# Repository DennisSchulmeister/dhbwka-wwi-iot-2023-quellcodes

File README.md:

Quellcodes zum Wahlmodul „IoT - Hardwarenahe Programmierung”
============================================================

Kurzbeschreibung
----------------

Dieses Repository beinhaltet sämtliche zur Verfügung gestellten Quellcodes,
Aufgaben und Praxisbeispiele des Wahlmoduls „IoT – Hardwarenahe Programmierung”
im Studiengang Wirtschaftsinformatik an der DHBW Karlsruhe.

Copyright
---------

Sämtliche Quellcodes sind lizenziert unter
[_Creative Commons Namensnennung 4.0 International_](http://creativecommons.org/licenses/by/4.0/)

© 2023 Dennis Schulmeister-Zimolong <br/>

E-Mail: [dhbw@windows3.de](mailto:dhbw@windows3.de) <br/>
Webseite: https://www.wpvs.de

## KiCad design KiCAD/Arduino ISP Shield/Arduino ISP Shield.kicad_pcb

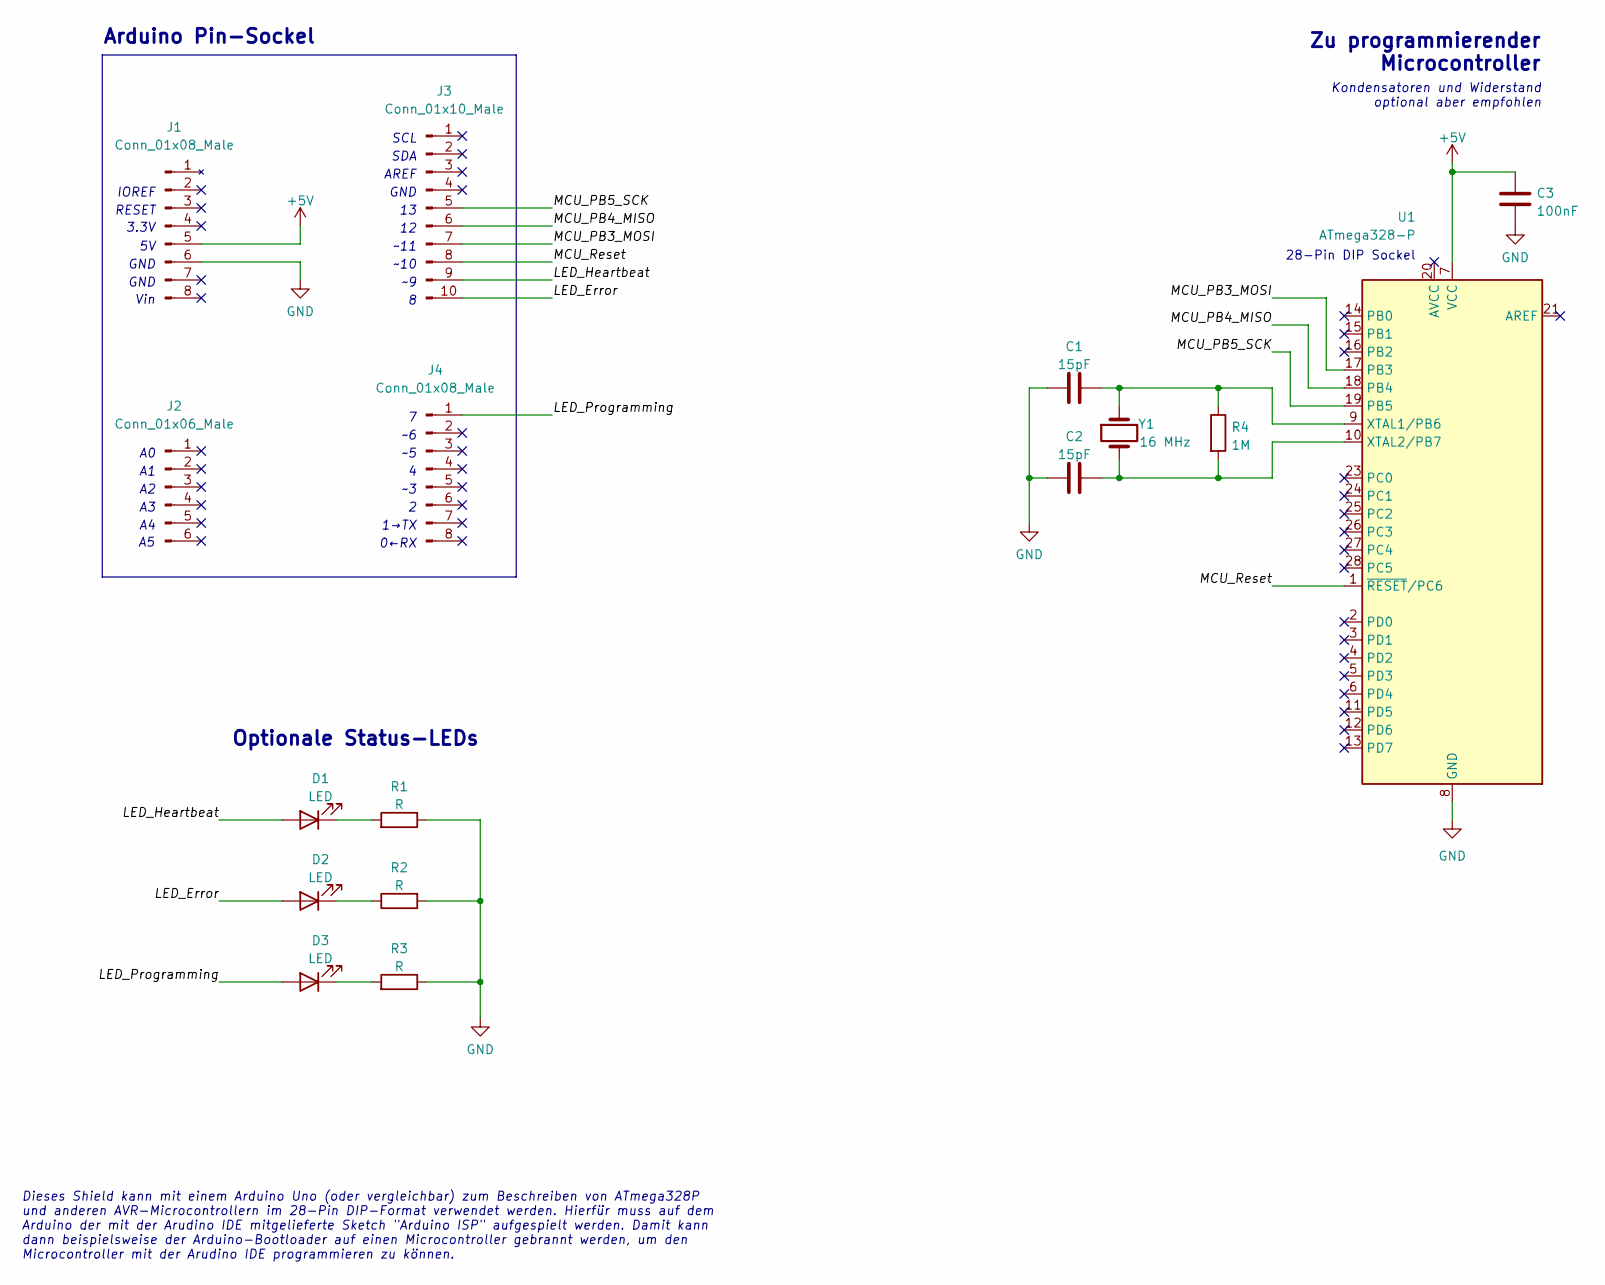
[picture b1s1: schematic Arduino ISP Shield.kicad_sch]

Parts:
C1, C2: 15pF; C_Disc_D5.0mm_W2.5mm_P5.00mm
C3: 100nF; C_Disc_D5.0mm_W2.5mm_P5.00mm
D1, D2, D3: LED; LED_D5.0mm
J1, J4: Conn_01x08_Male; PinHeader_1x08_P2.54mm_Vertical
J2: Conn_01x06_Male; PinHeader_1x06_P2.54mm_Vertical
J3: Conn_01x10_Male; PinHeader_1x10_P2.54mm_Vertical
R1, R2, R3: R; R_Axial_DIN0207_L6.3mm_D2.5mm_P7.62mm_Horizontal
R4: 1M; R_Axial_DIN0207_L6.3mm_D2.5mm_P7.62mm_Horizontal
U1: ATmega328-P; DIP-28_W7.62mm
Y1: 16 MHz; Resonator-2Pin_W8.0mm_H3.5mm

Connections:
+5V: C3.1, J1.5, U1.7 (VCC)
/LED_Error: D2.2 (A), J3.10
/LED_Heartbeat: D1.2 (A), J3.9
/LED_Programming: D3.2 (A), J4.1
/MCU_PB3_MOSI: J3.7, U1.17 (PB3)
/MCU_PB4_MISO: J3.6, U1.18 (PB4)
/MCU_PB5_SCK: J3.5, U1.19 (PB5)
/MCU_Reset: J3.8, U1.1 (~RESET/PC6)
GND: C1.1, C2.1, C3.2, J1.6, R1.1, R2.2, R3.1, U1.8 (GND), U1.22 (GND)
unnamed: C1.2, R4.1, U1.9 (XTAL1/PB6), Y1.1
unnamed: C2.2, R4.2, U1.10 (XTAL2/PB7), Y1.2
unnamed: D1.1 (K), R1.2
unnamed: D2.1 (K), R2.1
unnamed: D3.1 (K), R3.2

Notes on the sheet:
SCL
Kondensatoren und Widerstand optional aber empfohlen
Vin
Dieses Shield kann mit einem Arduino Uno (oder vergleichbar) zum Beschreiben von ATmega328P und anderen AVR-Microcontrollern im 28-Pin DIP-Format verwendet werden. Hierfür muss auf dem Arduino der mit der Arudino IDE mitgelieferte Sketch "Arduino ISP" aufgespielt werden. Damit kann dann beispielswe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
Arduino Pin-Sockel
SDA
0←RX
GND
AREF
Optionale Status-LEDs
Zu programmierender Microcontroller
28-Pin DIP Sockel
~10
IOREF
3.3V
~11
RESET
1→TX

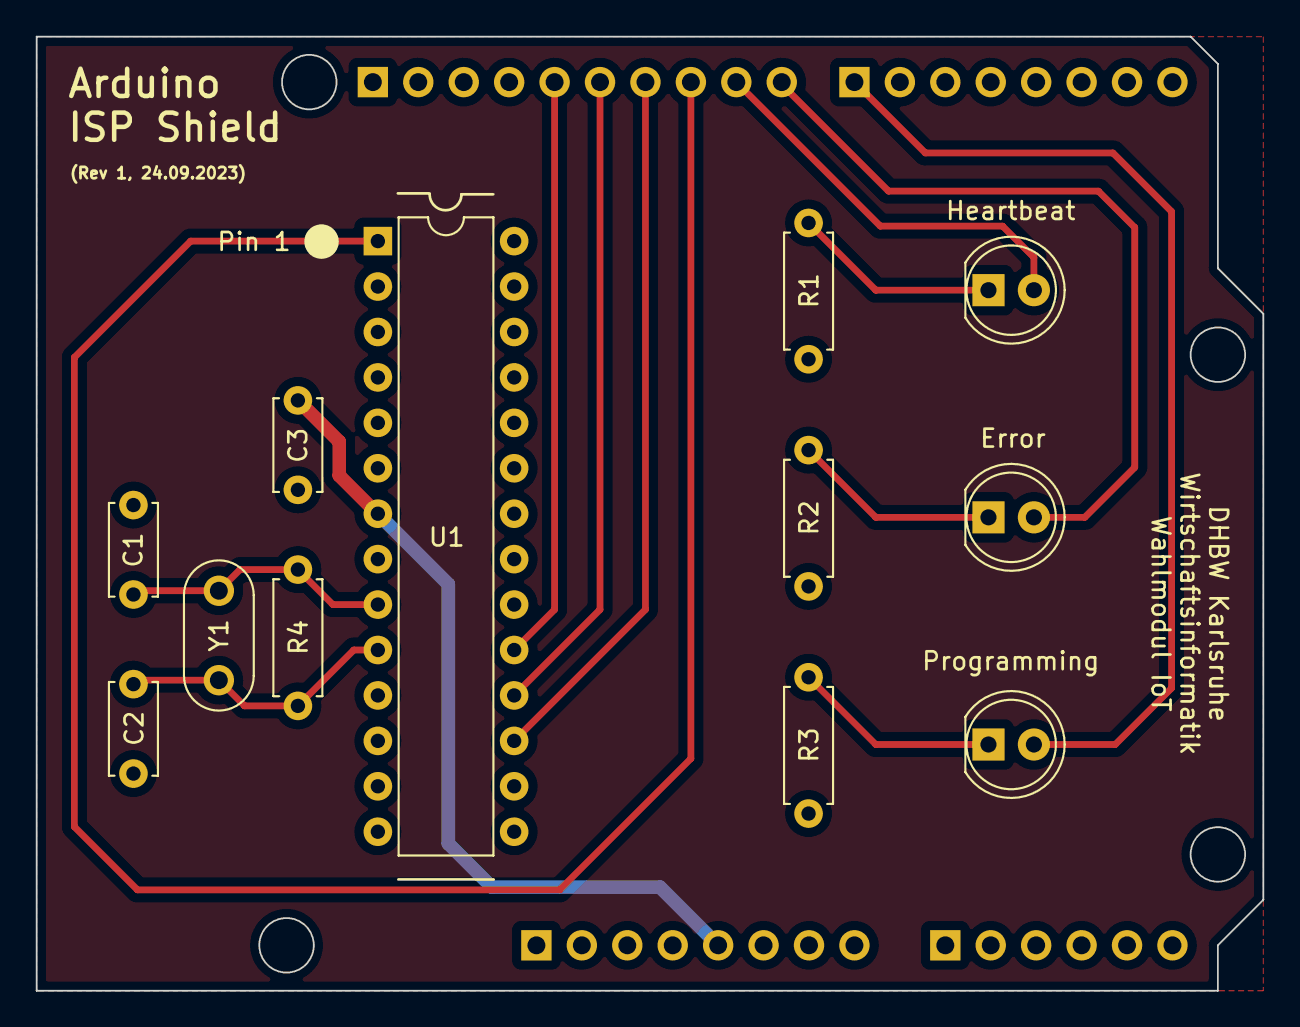
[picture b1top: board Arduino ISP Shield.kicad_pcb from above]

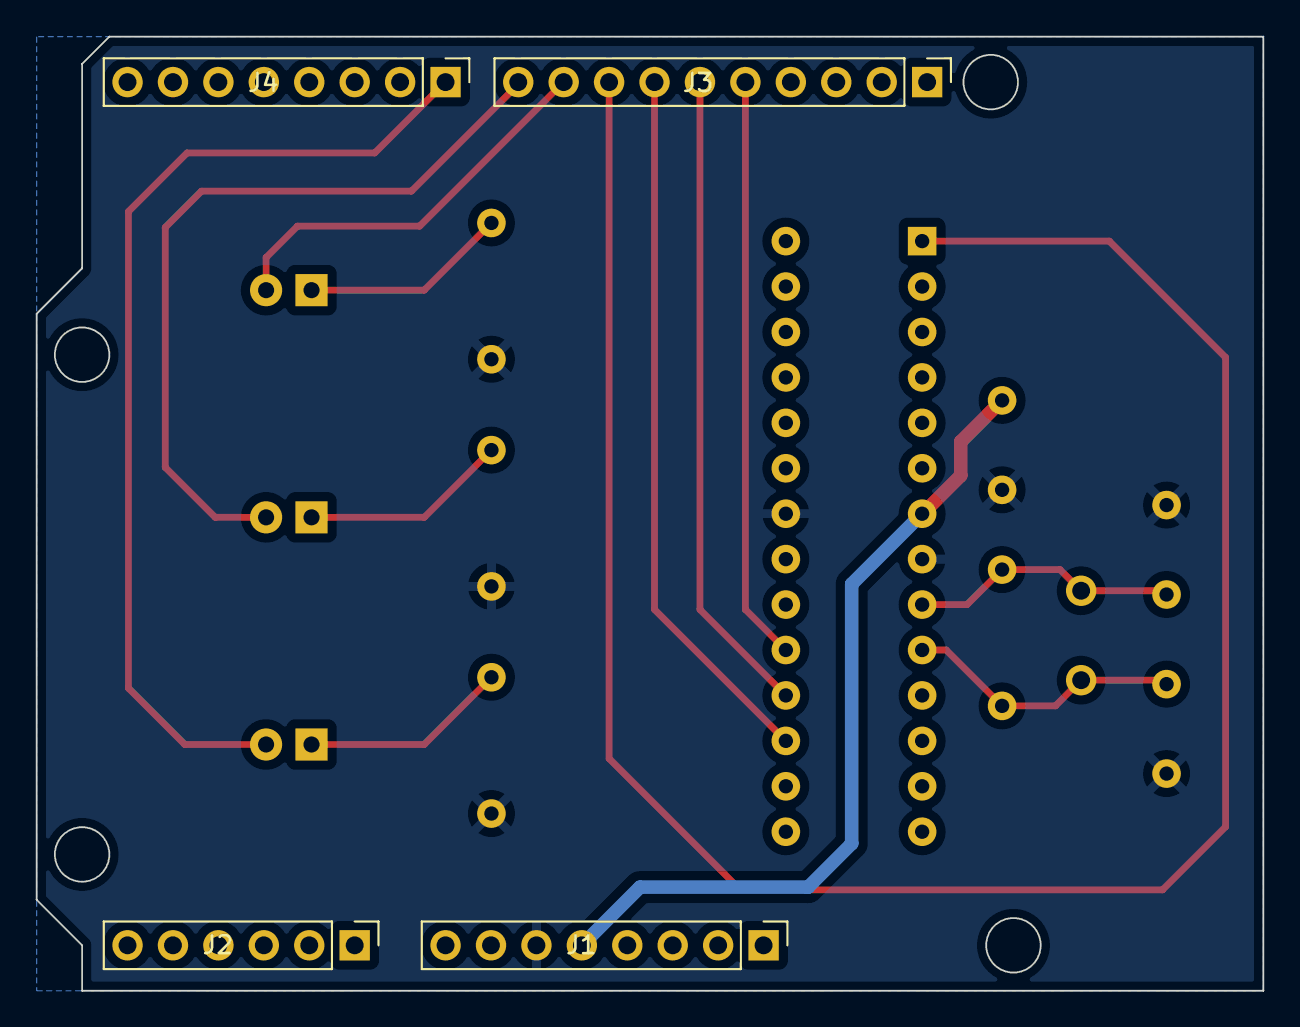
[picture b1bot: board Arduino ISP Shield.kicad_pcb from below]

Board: 2 copper layers, 68.6 x 53.3 mm, 16 parts (4 on the bottom side), 14 nets.

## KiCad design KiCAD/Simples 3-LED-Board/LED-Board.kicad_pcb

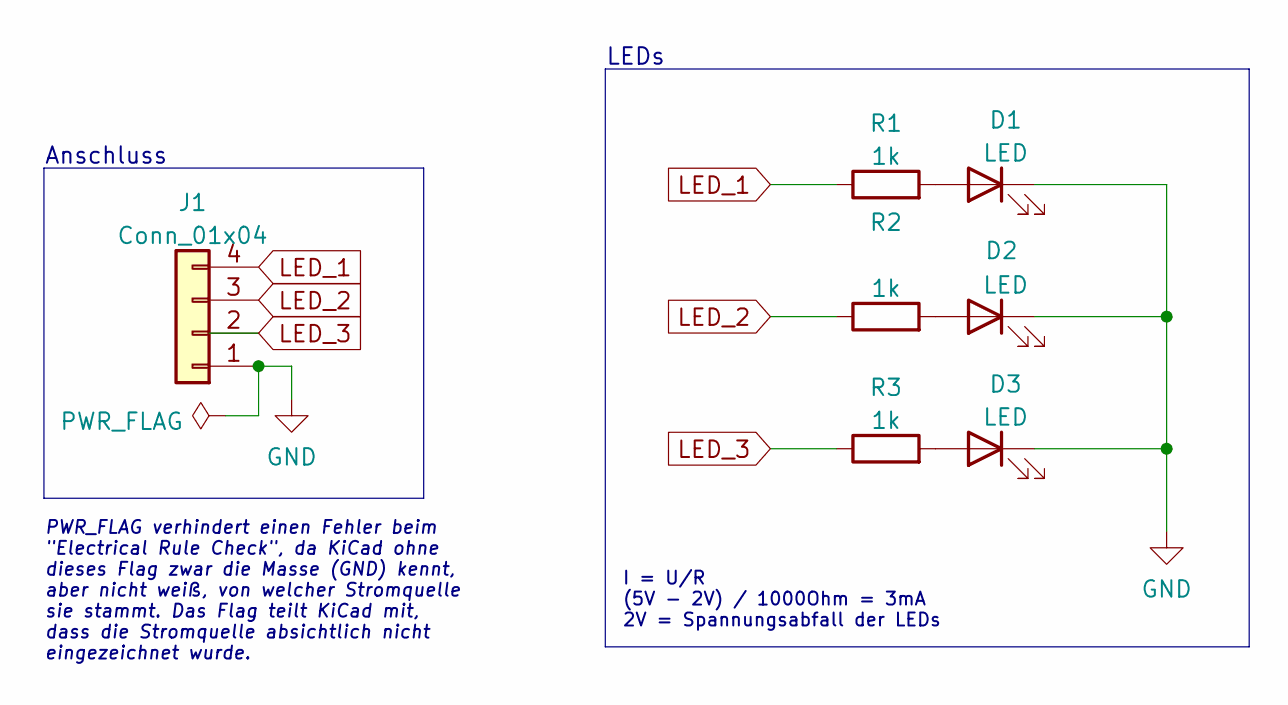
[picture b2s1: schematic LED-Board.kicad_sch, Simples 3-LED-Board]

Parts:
D1, D2, D3: LED; LED_D3.0mm
J1: Conn_01x04; PinHeader_1x04_P2.54mm_Vertical
R1, R2, R3: 1k; R_Axial_DIN0204_L3.6mm_D1.6mm_P5.08mm_Horizontal

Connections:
GND: D1.1 (K), D2.1 (K), D3.1 (K), J1.1
LED_1: J1.4, R1.1
LED_2: J1.3, R2.1
LED_3: J1.2, R3.1
unnamed: D1.2 (A), R1.2
unnamed: D2.2 (A), R2.2
unnamed: D3.2 (A), R3.2

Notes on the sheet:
I = U/R (5V - 2V) / 1000Ohm = 3mA 2V = Spannungsabfall der LEDs
Anschluss
PWR_FLAG verhindert einen Fehler beim "Electrical Rule Check", da KiCad ohne dieses Flag zwar die Masse (GND) kennt, aber nicht weiß, von welcher Stromquelle sie stammt. Das Flag teilt KiCad mit, dass die Stromquelle absichtlich nicht eingezeichnet wurde.
LEDs

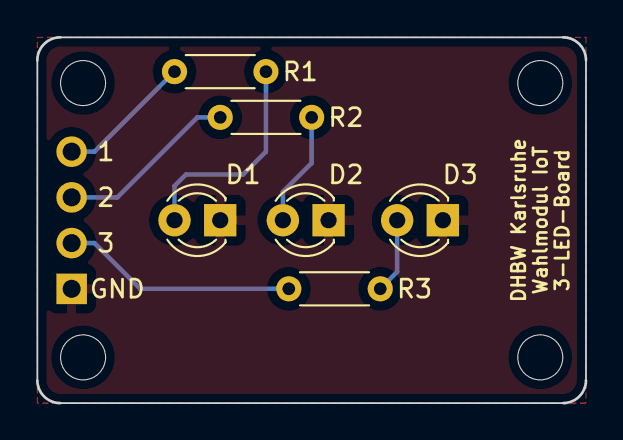
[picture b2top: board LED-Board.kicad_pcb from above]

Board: 2 copper layers, 30.5 x 20.3 mm, 11 parts (1 on the bottom side), 7 nets.

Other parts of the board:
H1, H2, H3, H4: MountingHole; MountingHole_2.5mm

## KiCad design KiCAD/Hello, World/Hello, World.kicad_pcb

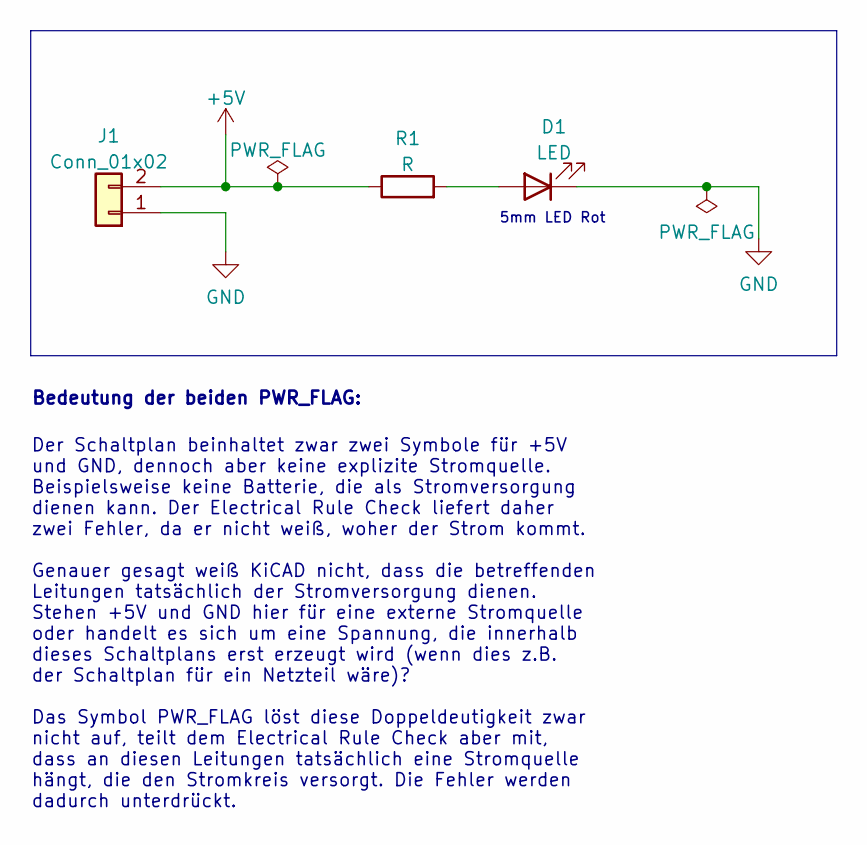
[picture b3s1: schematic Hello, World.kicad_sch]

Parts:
D1: LED; LED_D8.0mm
J1: Conn_01x02; TerminalBlock_bornier-2_P5.08mm
R1: R; R_Axial_DIN0204_L3.6mm_D1.6mm_P5.08mm_Horizontal

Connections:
+5V: J1.2, R1.1
GND: D1.1 (K), J1.1
unnamed: D1.2 (A), R1.2

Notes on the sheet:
Bedeutung der beiden PWR_FLAG:
Der Schaltplan beinhaltet zwar zwei Symbole für +5V und GND, dennoch aber keine explizite Stromquelle. Beispielsweise keine Batterie, die als Stromversorgung dienen kann. Der Electrical Rule Check liefert daher zwei Fehler, da er nicht weiß, woher der Strom kommt. Genauer gesagt weiß KiCAD nicht, d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
5mm LED Rot

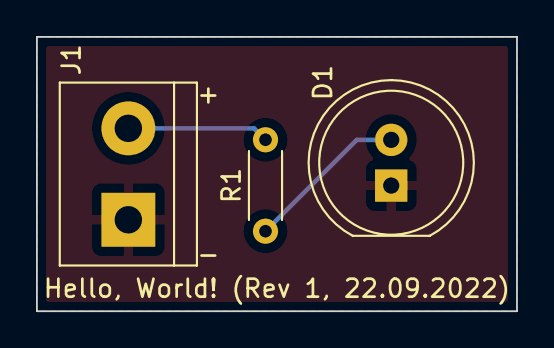
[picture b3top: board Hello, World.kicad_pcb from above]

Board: 2 copper layers, 26.7 x 15.2 mm, 3 parts (0 on the bottom side), 3 nets.

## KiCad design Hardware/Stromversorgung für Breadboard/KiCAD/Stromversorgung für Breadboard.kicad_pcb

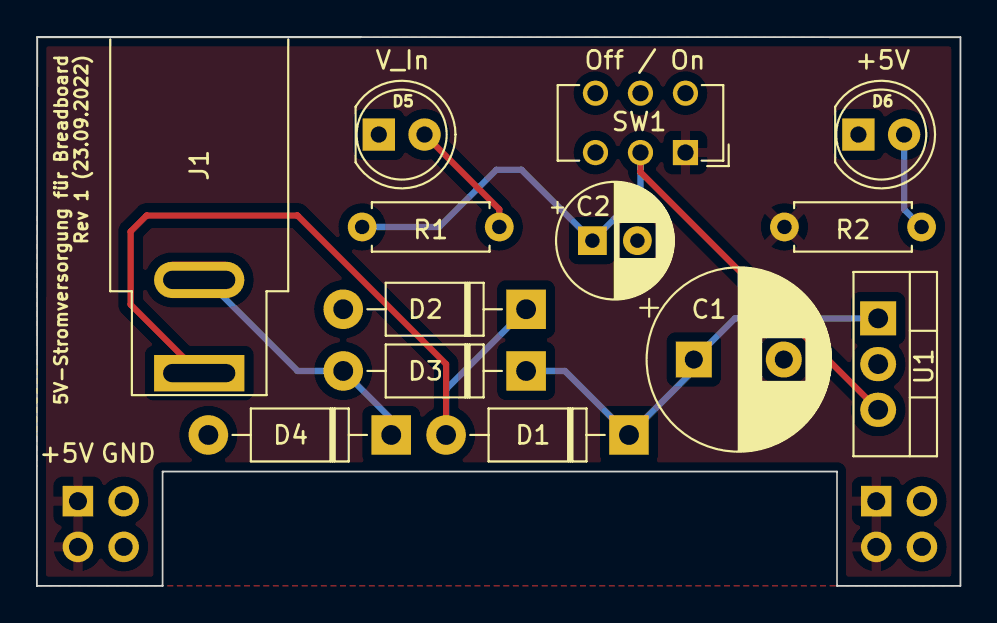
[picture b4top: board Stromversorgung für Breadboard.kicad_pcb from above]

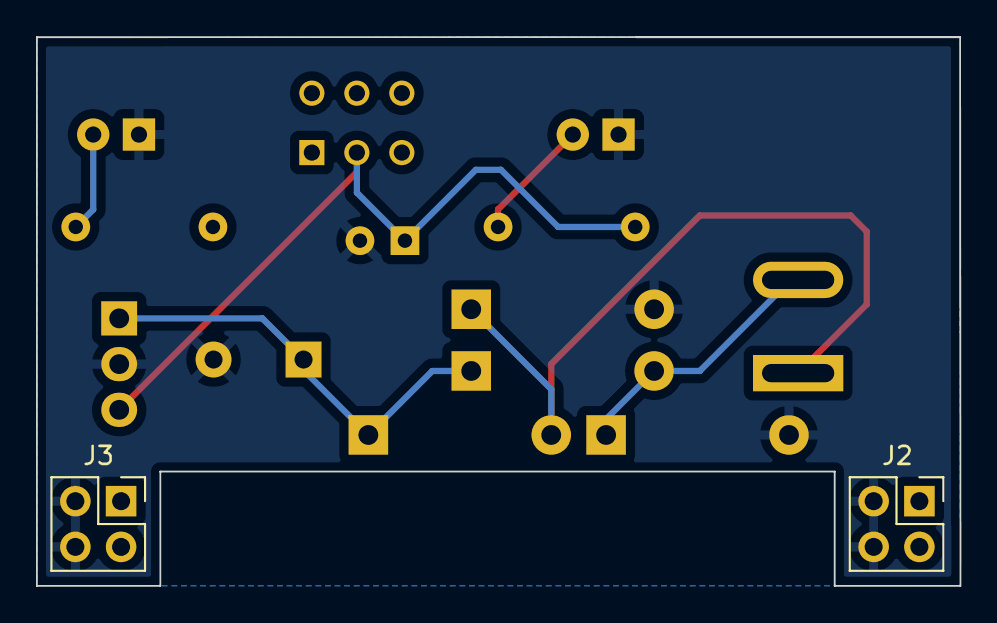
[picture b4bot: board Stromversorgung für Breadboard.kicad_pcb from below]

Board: 2 copper layers, 51.3 x 30.5 mm, 15 parts (2 on the bottom side), 8 nets.

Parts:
C1: 470µ; CP_Radial_D10.0mm_P5.00mm
C2: 47µ; CP_Radial_D6.3mm_P2.50mm
D1, D2, D3, D4: 1N4007; D_DO-41_SOD81_P10.16mm_Horizontal
D5, D6: LED; LED_D5.0mm
J1: Barrel_Jack; BarrelJack_SwitchcraftConxall_RAPC10U_Horizontal
J2, J3: Conn_02x02_Odd_Even; PinHeader_2x02_P2.54mm_Vertical
R1, R2: 560; R_Axial_DIN0207_L6.3mm_D2.5mm_P7.62mm_Horizontal
SW1: SW_DPDT_x2; SW_CuK_JS202011CQN_DPDT_Straight
U1: LM7805_TO220; TO-220-3_Vertical

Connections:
/GND: C1.2, C2.2, D2.2 (A), D4.2 (A), D5.1 (K), D6.1 (K), J2.3, J2.4, J3.3, J3.4, U1.2 (GND)
/V_in: C1.1, D1.1 (K), D3.1 (K), U1.1 (VI)
/V_out1: C2.1, R1.1, SW1.2 (B), U1.3 (VO)
/V_out2: J2.1, J2.2, J3.1, J3.2, R2.1, SW1.1 (A)
unnamed: D1.2 (A), D2.1 (K), J1.1
unnamed: D3.2 (A), D4.1 (K), J1.2
unnamed: D5.2 (A), R1.2
unnamed: D6.2 (A), R2.2

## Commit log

2023-09-14 Initialer Commit
2023-09-14 Hardwareskizzen für die Button-Beispiele
2023-09-14 .arduino Tempdateien gelöscht
2023-09-14 .gitignore um .arduino ergänzt
2023-09-20 Rasbperry Pi: Execute-Flag für alle Dateien korrigiert
2023-09-21 Raspberry Pi: wpa_supplicant.conf
2023-09-21 Raspberry Pi: Debugging
2023-09-24 KiCAD-Beispiel für Arduino ISP Board, Aufräumen der anderen KiCAD-Beispiele
2023-09-28 Eigenes Verzeichnis für CircuitJS
2023-09-30 Arduino ISP: Fehlende Widerstandswerte
2023-10-04 CircuitJS: Grundlagen der Elektronik (wip)
2023-10-04 CircuitJS: Reihenschaltung mehrerer Verbraucher
2023-10-04 CircuitJS: Praktische Anwendung von Spannungsteilern
2023-10-04 CircuitJS: Reihen- und Parallelschaltung gleichzeitig!
2023-10-04 CircuitJS: Reihen- und Parallelschaltung gleichzeitig
2023-10-04 CircuitJS: Spannungsteiler - leere Batterie
2023-10-04 Digitalsignale mit dem Microcontroller erzeugen
2023-10-04 CircuitJS: Große Lasten Schalten mit Transistor
2023-10-04 CircuitJS: Große Lasten schalten mit Relais
2023-10-04 CircuitJS: Spannungsregelung mit Pulsweitenmodulation
2023-10-05 CircuitJS: Digitalsignale mit dem Microcontroller auswerten
2023-10-05 CircuitJS: Grundlagen der Elektronik (kleinere Korrekturen)
2023-10-05 CircuitJS: Widerstand → Typische Fragen
2023-10-05 CircuitJS: Anpassungen
2023-10-06 CircuitJS: Kleine Tippfehle
2023-10-26 Überarbeitete und weitere Beispiele
2023-10-26 LED-Matrix: Hilfsprogramm zum Debuggen der Hardwareschaltung
2023-11-02 Neue Aufgaben und Beispiele
2023-11-02 Neuste Anpassungen
2023-11-02 Einreihen des PWM-Analogsignal Beispiels
2023-11-02 Helligkeitsregler: Fehler in der Musterlösung
2024-02-08 LED-Helligkeitsregler: Skizze mit Atmega auf Breadboard
2024-02-11 ESP32: Erste Beispiele
2024-02-11 ESP32: Tastatureingaben
2024-02-11 ESP32 Multitasking: xPortGetCoreID()
2024-02-11 Umbennenung der Arduino Uno und ESP32 Verzeichnisse
2024-02-11 Includes verschoben, damit sie von der Arduino IDE automatisch geöffnet werden
2024-02-12 Arduino ESP32: Beispiel für FAT-Dateisystem
2024-02-13 ESP32: Web File Manager (wip)
2024-02-15 Raspi-Beispiele: Bessere Hardwareskizzen
2024-02-15 Grundstruktur für C++ Crashkurs
2024-02-15 ESP32: Web File Manager (kompiliert nicht)
2024-02-15 .old Datei gelöscht
2024-02-15 C/C++ Crashkurs: Quellcodemodularisierung
2024-02-15 C++ Crashkurs: Konstanten
2024-02-15 C++ Crashkurs: Zeiger und Referenzen
2024-02-15 C++ Crashkurs Zeiger 2: Typos
2024-02-22 Restliche Beispiele für den C++ Crashkurs
2024-02-22 .gitkeep-Dateien entfernt
2024-02-22 C++ Crashkurs: Redundantes Logging-Beispiel entfernt
2024-02-29 ESP32: MQTT-Client
2024-03-02 ESP32: Webradio
2024-03-07 ESP32: ThingsBoard-Beispiel
2024-03-07 .gitkeep
2024-03-07 wifi-connect.h: c_str()
2024-03-14 ESP32-Thingsboard: Vollständiges Beispiel
2024-03-22 ESP32 Webradio: Pin-Belegung
2024-04-03 Neues Beispiel: LCD-Display (HD44780) mit ESP32
2024-04-04 ESP32: Timer Interrupt
2024-04-04 ESP32: Soundsensor / Loudness-Meter
2024-04-04 Kleinmembran-Kondensatormikrofon
2024-10-01 Library Updates
2024-10-01 Arduino Uno: Trennung nach Aufgaben und Beispielen
2024-10-02 Arduino Uno: Neue Beispiele
2024-10-02 Kleinere Korrekturen an den neuen Beispielen
2024-10-02 Drehpoit: Fehler in der Skizze
2024-10-09 Arduino Uno / Analogeingang: CircuitJS für Buttons aktualisiert
2024-10-09 Arduino Uno / Analogeingang: Buttos weiter vereinfacht
2024-10-24 Neue Beispiele
2024-10-24 Musterlösungen: 2 Buttons, Nachtlicht
2024-11-03 Buttons entprellen
2024-11-06 Beispiel: Serial Chat (wip)
2024-11-07 Serial Chat fertig
2024-11-07 SoftwareSerial und Skizze zu Serial_Chat
2024-11-07 Neues Beispiel: LCD-Display HD44780
2024-11-09 HD44780-Beispiel: Kommentar zum Hardwareaufbau
2024-11-11 Neues Beispiel: Atmega-Serial-Display
2025-02-06 Kurzschluss bei Stromversorgung in den Arduni Uno Beispiele korrigiert
2025-02-06 Drehpoti LED-Bar Hardwareskizze
2025-03-20 ESP32 ThingsBoard
2025-07-22 WIFI: WPA3
2025-09-21 Atmega Serial Display: Mini Tippfehler in der Doku
